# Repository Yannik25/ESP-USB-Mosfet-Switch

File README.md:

# ESP USB/Mosfet Switch
 
 A small PCB, based on an ESP12E to switch USB or general 3.3V / 5V devices via Headers.
 Created with KiCad
 
## Current status: Ordered 
 
## Features

- 1. Multiple input selection
   - 12V/5V/3.3V via Headers
   - 5V via micro USB
   - 5V via USB-C

- 2. Multiple output selection
   - 12V/5V/3.3V via Headers (selectable via solderjumper)
   - 5V via USB-A 
   - 5V via USB-C
   
- 3. Read Current via INA226

- 4. Onboard WS2812B LED
	- control additional digital LEDs

## The Hardware:

## Example configuration

```yaml
# Configuration for ESPHOME
```

## Contributions

Feel free to open Pull Requests here

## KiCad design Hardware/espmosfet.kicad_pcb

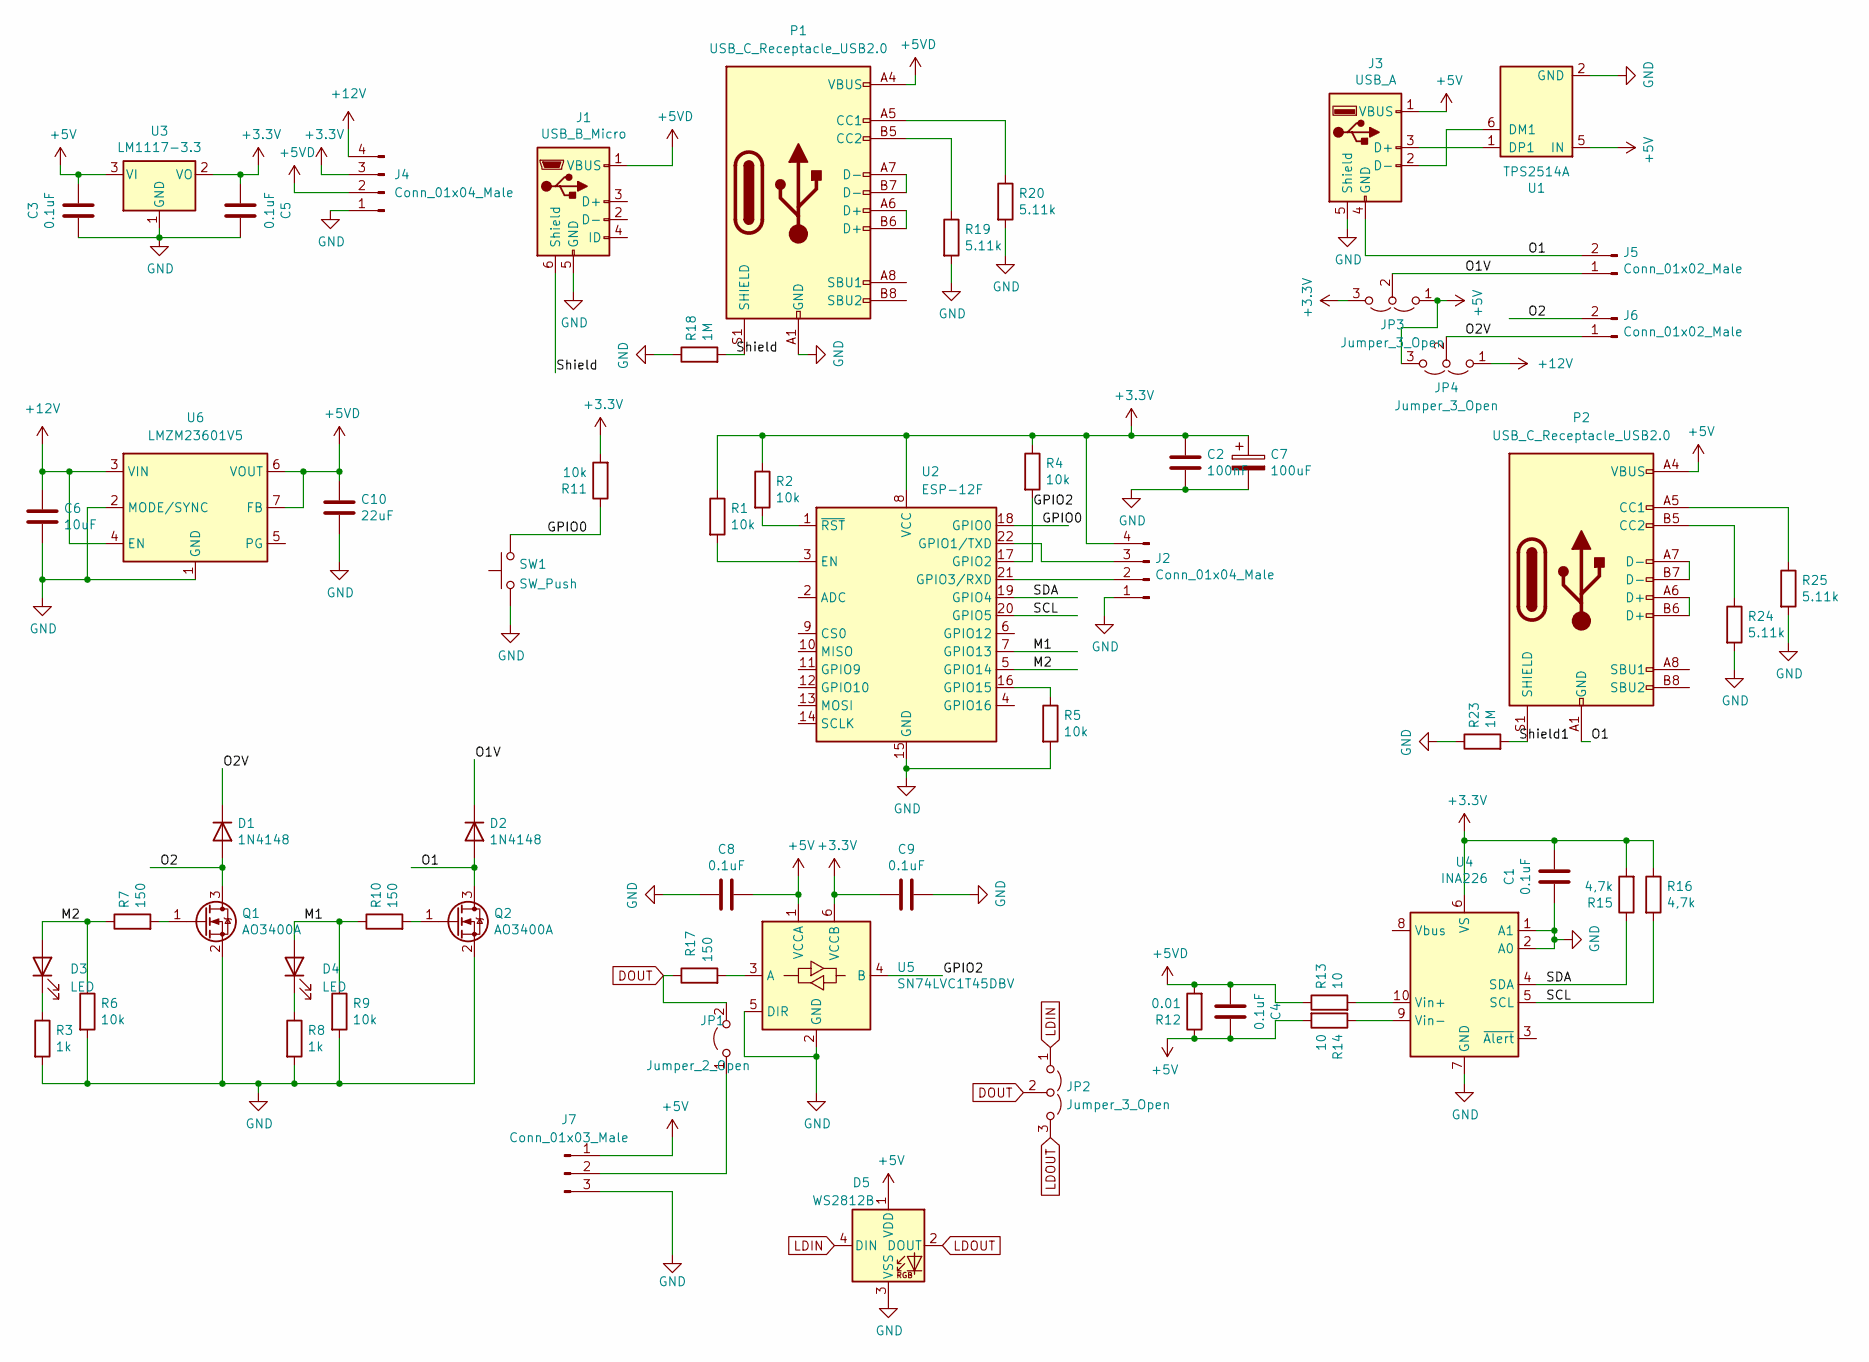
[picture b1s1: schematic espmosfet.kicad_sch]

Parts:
C1, C3, C4, C5: 0.1uF; C_0805_2012Metric
C2: 100nF; C_0805_2012Metric
C6: 10uF; C_0603_1608Metric
C7: 100uF; CP_EIA-3216-18_Kemet-A
C8, C9: 0.1uF; C_0603_1608Metric
C10: 22uF; C_0805_2012Metric
D1, D2: 1N4148; D_1206_3216Metric
D3, D4: LED; LED_0603_1608Metric
D5: WS2812B; LED_WS2812B_PLCC4_5.0x5.0mm_P3.2mm
J1: USB_B_Micro; USB_Micro-B_Molex_47346-0001
J2: Conn_01x04_Male; PinHeader_1x04_P2.54mm_Vertical
J3: USB_A; USB_A_Stewart_SS-52100-001_Horizontal
J4: Conn_01x04_Male; PinHeader_1x04_P2.54mm_Horizontal
J5, J6: Conn_01x02_Male; PinHeader_1x02_P2.54mm_Vertical
J7: Conn_01x03_Male; PinHeader_1x03_P2.54mm_Vertical
JP1: Jumper_2_Open; SolderJumper-2_P1.3mm_Open_Pad1.0x1.5mm
JP2, JP3, JP4: Jumper_3_Open; SolderJumper-3_P1.3mm_Open_Pad1.0x1.5mm
P1, P2: USB_C_Receptacle_USB2.0; USB_C_Receptacle_XKB_U262-16XN-4BVC11
Q1, Q2: AO3400A; SOT-23
R1, R2, R4, R5, R6, R9, R11: 10k; R_0805_2012Metric
R3, R8: 1k; R_0805_2012Metric
R7, R10, R17: 150; R_0805_2012Metric
R12: 0.01; R_0805_2012Metric
R13, R14: 10; R_0805_2012Metric
R15, R16: 4,7k; R_0805_2012Metric
R18, R23: 1M; R_0805_2012Metric
R19, R20, R24, R25: 5.11k; R_0603_1608Metric
SW1: SW_Push; SW_Push_SPST_NO_Alps_SKRK
U1: TPS2514A; SOT-23-6
U2: ESP-12F; ESP-12E
U3: LM1117-3.3; SOT-223
U4: INA226; VSSOP-10_3x3mm_P0.5mm
U5: SN74LVC1T45DBV; SOT-23-6
U6: LMZM23601V5; Texas_SIL0010A_MicroSiP-10-1EP_3.8x3mm_P0.6mm_EP0.7x2.9mm_T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

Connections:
+3V3: C1.1, C2.1, C5.2, C7.1, C9.2, J2.4, J4.3, JP3.3 (B), R1.1, R2.1, R4.1, R11.2, R15.2, R16.1, U2.8 (VCC), U3.2 (VO), U4.6 (VS), U5.6 (VCCB)
+5V: C3.1, C4.1, C8.1, D5.1 (VDD), J3.1 (VBUS), J7.1, JP3.1 (A), JP4.3 (B), P2.A4 (VBUS), P2.A9 (VBUS), P2.B4 (VBUS), P2.B9 (VBUS), R12.1, R14.2, U1.5 (IN), U3.3 (VI), U5.1 (VCCA)
+5VD: C4.2, C10.1, J1.1 (VBUS), J4.2, P1.A4 (VBUS), P1.A9 (VBUS), P1.B4 (VBUS), P1.B9 (VBUS), R12.2, R13.1, U6.6 (VOUT), U6.7 (FB)
+12V: C6.1, J4.4, JP4.1 (A), U6.3 (VIN), U6.4 (EN)
/GPIO0: R11.1, SW1.2, U2.18 (GPIO0)
/GPIO2: R4.2, U2.17 (GPIO2), U5.4 (B)
/M1: D4.2 (A), R9.1, R10.1, U2.7 (GPIO13)
/M2: D3.2 (A), R6.1, R7.1, U2.5 (GPIO14)
/O1: D2.2 (A), J3.4 (GND), J5.2, P2.A1 (GND), P2.A12 (GND), P2.B1 (GND), P2.B12 (GND), Q2.3 (D)
/O1V: D2.1 (K), J5.1, JP3.2 (C)
/O2: D1.2 (A), J6.2, Q1.3 (D)
/O2V: D1.1 (K), J6.1, JP4.2 (C)
/SCL: R16.2, U2.20 (GPIO5), U4.5 (SCL)
/SDA: R15.1, U2.19 (GPIO4), U4.4 (SDA)
/Shield: J1.6 (Shield), P1.S1 (SHIELD), R18.2
/Shield1: P2.S1 (SHIELD), R23.2
DOUT: JP1.2 (B), JP2.2 (C), R17.1
GND: C1.2, C2.2, C3.2, C5.1, C6.2, C7.2, C8.2, C9.1, C10.2, D5.3 (VSS), J1.5 (GND), J2.1, J3.5 (Shield), J4.1, J7.3, P1.A1 (GND), P1.A12 (GND), P1.B1 (GND), P1.B12 (GND), Q1.2 (S), Q2.2 (S), R3.2, R5.2, R6.2, R8.2, R9.2, R18.1, R19.2, R20.2, R23.1, R24.2, R25.2, SW1.1, U1.2 (GND), U2.15 (GND), U3.1 (GND), U4.1 (A1), U4.2 (A0), U4.7 (GND), U5.2 (GND), U5.5 (DIR), U6.1 (GND), U6.2 (MODE/SYNC), U6.11 (GND)
LDIN: D5.4 (DIN), JP2.1 (A)
LDOUT: D5.2 (DOUT), JP2.3 (B)
unnamed: D3.1 (K), R3.1
unnamed: D4.1 (K), R8.1
unnamed: J2.2, U2.21 (GPIO3/RXD)
unnamed: J2.3, U2.22 (GPIO1/TXD)
unnamed: J3.2 (D-), U1.6 (DM1)
unnamed: J3.3 (D+), U1.1 (DP1)
unnamed: J7.2, JP1.1 (A)
unnamed: P1.A5 (CC1), R20.1
unnamed: P1.A6 (D+), P1.B6 (D+)
unnamed: P1.A7 (D-), P1.B7 (D-)
unnamed: P1.B5 (CC2), R19.1
unnamed: P2.A5 (CC1), R25.1
unnamed: P2.A6 (D+), P2.B6 (D+)
unnamed: P2.A7 (D-), P2.B7 (D-)
unnamed: P2.B5 (CC2), R24.1
unnamed: Q1.1 (G), R7.2
unnamed: Q2.1 (G), R10.2
unnamed: R1.2, U2.3 (EN)
unnamed: R2.2, U2.1 (~RST)
unnamed: R5.1, U2.16 (GPIO15)
unnamed: R13.2, U4.10 (Vin+)
unnamed: R14.1, U4.9 (Vin-)
unnamed: R17.2, U5.3 (A)

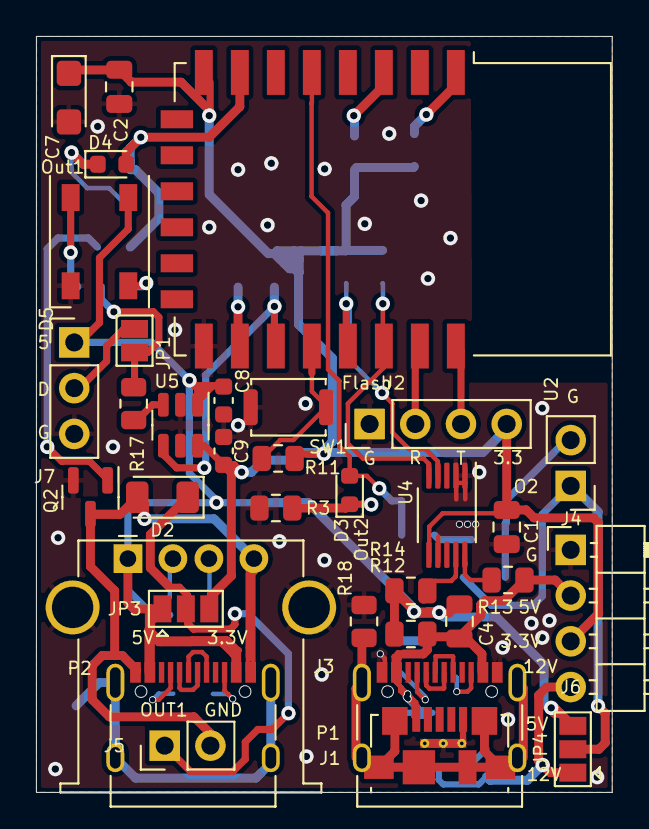
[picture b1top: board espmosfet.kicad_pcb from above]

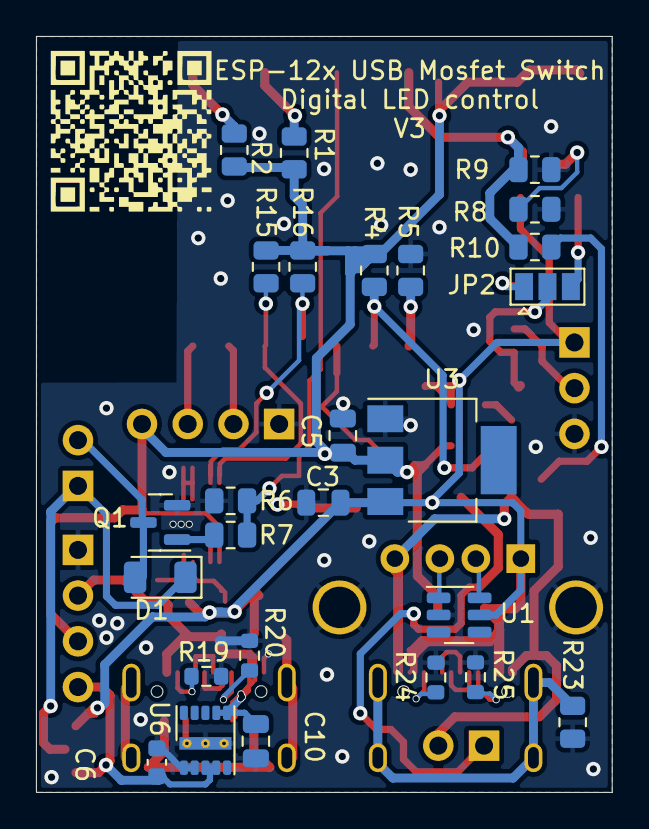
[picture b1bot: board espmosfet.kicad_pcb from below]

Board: 2 copper layers, 32.0 x 42.0 mm, 60 parts (26 on the bottom side), 43 nets.

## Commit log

2021-12-14 add initial hardware version
2021-12-22 add information, pictures and models
2021-12-22 fix image
2021-12-24 fix case size
2022-01-10 update sch and pcb, fix mosfet, add 12V option, add digital led pins
2022-01-10 cleanup
2022-01-10 add USB-C input
2022-01-11 add ws2812b on board, add USB-C Output
2022-01-11 add schematics pdf
2022-01-11 update to V2 Version
2022-01-11 adjust Readme
2022-01-28 Create LICENSE
2022-02-04 add gerber
2022-05-09 fix ws2812b pinout, change to open jumpers
2022-05-13 update gerber
